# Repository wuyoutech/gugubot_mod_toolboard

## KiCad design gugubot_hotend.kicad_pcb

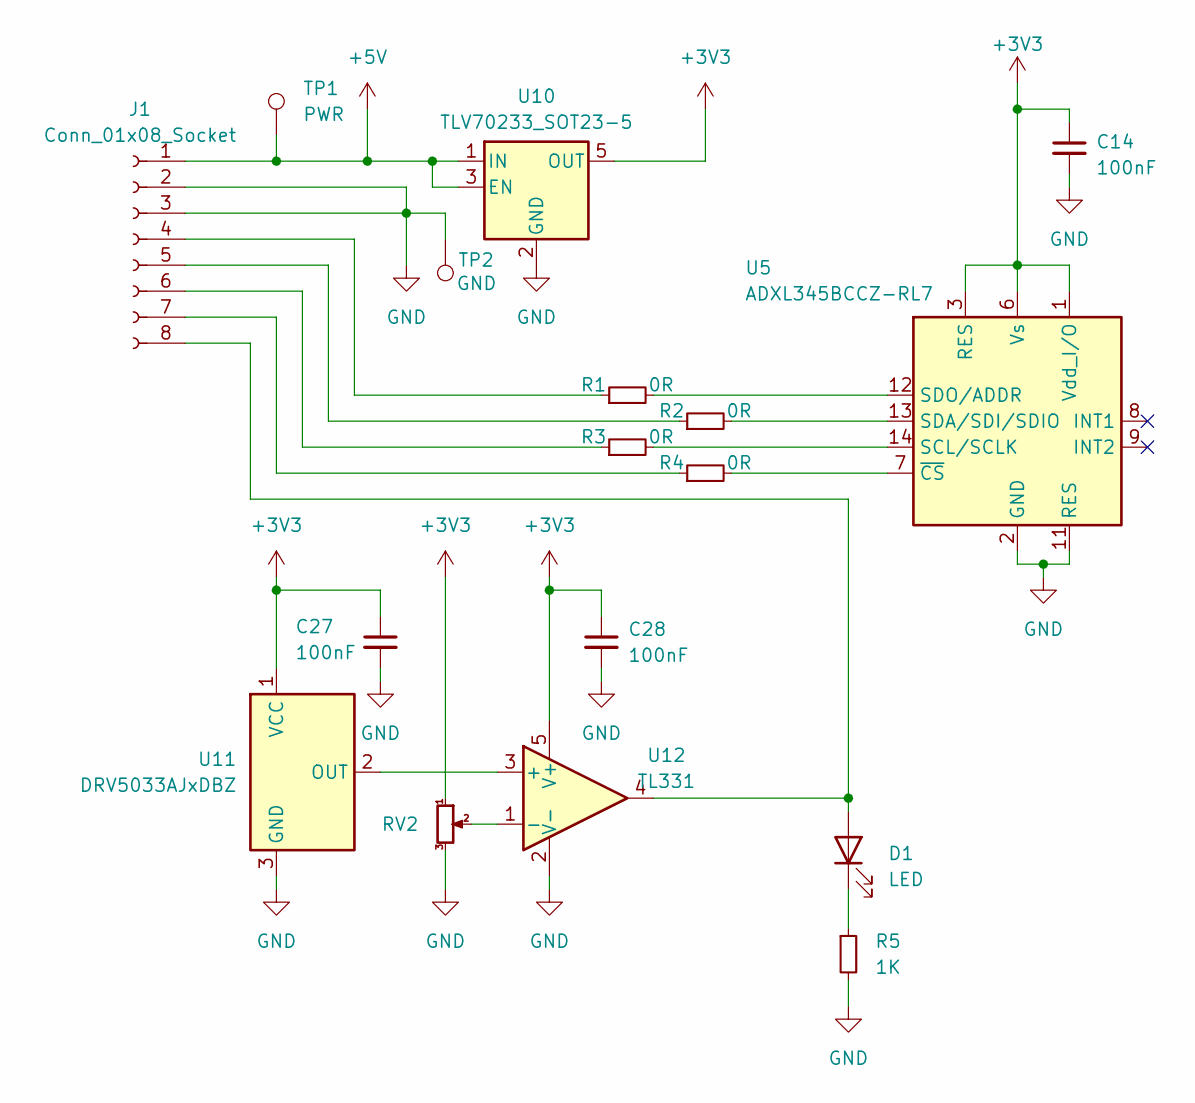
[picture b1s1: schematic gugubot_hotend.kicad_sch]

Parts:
C14, C27, C28: 100nF; C_0402_1005Metric
D1: LED; LED_0603_1608Metric
J1: Conn_01x08_Socket; JST_GH_SM08B-GHS-TB_1x08-1MP_P1.25mm_Horizontal
R1, R2, R3, R4: 0R; R_0402_1005Metric
R5: 1K; R_0402_1005Metric
RV2: R_Potentiometer_Small; Potentiometer_Bourns_TC33X_Vertical
TP1: PWR; TestPoint_Pad_2.0x2.0mm
TP2: GND; TestPoint_Pad_2.0x2.0mm
U5: ADXL345BCCZ-RL7; LGA-14_3x5mm_P0.8mm_LayoutBorder1x6y
U10: TLV70233_SOT23-5; SOT-23-5
U11: DRV5033AJxDBZ; SOT-23
U12: TL331; SOT-23-5

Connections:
+3V3: C14.1, C27.1, C28.1, RV2.1, U5.1 (Vdd_I/O), U5.3 (RES), U5.6 (Vs), U10.5 (OUT), U11.1 (VCC), U12.5 (V+)
+5V: J1.1, TP1.1, U10.1 (IN), U10.3 (EN)
GND: C14.2, C27.2, C28.2, J1.2, J1.3, R5.2, RV2.3, TP2.1, U5.2 (GND), U5.4 (GND), U5.5 (GND), U5.11 (RES), U10.2 (GND), U11.3 (GND), U12.2 (V-)
unnamed: D1.2 (A), J1.8, U12.4
unnamed: D1.1 (K), R5.1
unnamed: J1.4, R1.1
unnamed: J1.5, R2.1
unnamed: J1.6, R3.1
unnamed: J1.7, R4.1
unnamed: R3.2, U5.14 (SCL/SCLK)
unnamed: R2.2, U5.13 (SDA/SDI/SDIO)
unnamed: R1.2, U5.12 (SDO/ADDR)
unnamed: R4.2, U5.7 (~CS)
unnamed: U11.2 (OUT), U12.3 (+)
unnamed: RV2.2, U12.1 (-)

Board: 4 copper layers, 17 parts (0 on the bottom side), 15 nets, no tracks yet.

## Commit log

2023-10-12 update bom
2023-11-04 add gitignore
2023-11-04 fix bom number bug
2024-04-27 add hall board
